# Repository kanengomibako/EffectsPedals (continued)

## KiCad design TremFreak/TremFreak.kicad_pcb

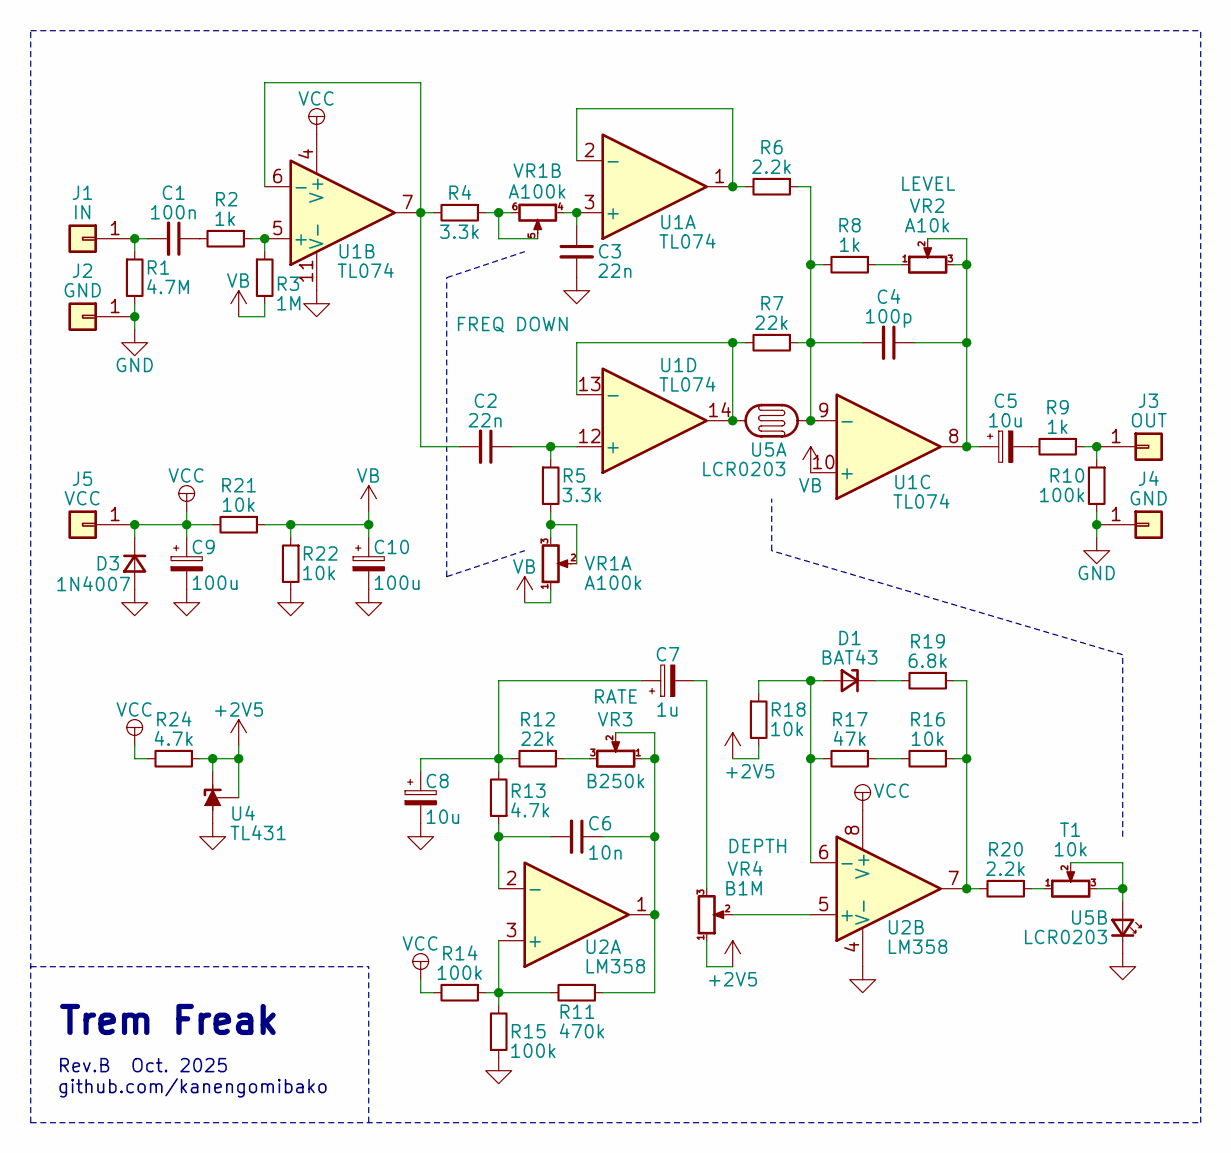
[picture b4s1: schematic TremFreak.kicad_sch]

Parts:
C1: 100n; my_C_Rect1_P5.00mm
C2, C3: 22n; my_C_Rect1_P5.00mm
C4: 100p; my_C_Rect1_P5.00mm
C5, C8: 10u; my_C_D5.0mm_P2.50mm
C6: 10n; my_C_Rect1_P5.00mm
C7: 1u; my_C_D5.0mm_P2.50mm
C9, C10: 100u; my_C_D6.3mm_P2.50mm
D1: BAT43; my_D_P7.62mm
D3: 1N4007; my_D_P7.62mm
J1: IN; my_WirePad_1mmDrill
J2, J4: GND; my_WirePad_1mmDrill
J3: OUT; my_WirePad_1mmDrill
J5: VCC; my_WirePad_1mmDrill
R1: 4.7M; my_R_P7.62mm_Horizontal
R2, R8, R9: 1k; my_R_P7.62mm_Horizontal
R3: 1M; my_R_P7.62mm_Horizontal
R4, R5: 3.3k; my_R_P7.62mm_Horizontal
R6, R20: 2.2k; my_R_P7.62mm_Horizontal
R7, R12: 22k; my_R_P7.62mm_Horizontal
R10, R14, R15: 100k; my_R_P7.62mm_Horizontal
R11: 470k; my_R_P7.62mm_Horizontal
R13, R24: 4.7k; my_R_P7.62mm_Horizontal
R16, R18, R21, R22: 10k; my_R_P7.62mm_Horizontal
R17: 47k; my_R_P7.62mm_Horizontal
R19: 6.8k; my_R_P7.62mm_Horizontal
T1: 10k; my_trim
U1: TL074; DIP-14_W7.62mm_Socket
U2: LM358; DIP-8_W7.62mm_Socket
U4: TL431; TO-92_Inline_Wide
U5: LCR0203
VR1: A100k; my_pot_5mm_dual
VR2: A10k; my_pot_5mm
VR3: B250k; my_pot_5mm
VR4: B1M; my_pot_5mm

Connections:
+2V5: R18.2, R24.1, U4.1 (REF), U4.3 (K), VR4.1
GND: C3.2, C8.2, C9.2, C10.2, D3.2 (A), J2.1, J4.1, R1.2, R10.2, R15.1, R22.2, U1.11 (V-), U2.4 (V-), U4.2 (A), U5.2
unnamed: C1.1, R2.2
unnamed: C4.1, C5.1, U1.8, VR2.2, VR2.3
unnamed: C5.2, R9.2
unnamed: C6.1, R11.1, U2.1, VR3.1, VR3.2
unnamed: C7.1, C8.1, R12.2, R13.2
unnamed: C7.2, VR4.3
unnamed: D1.2 (A), R17.2, R18.1, U2.6 (-)
unnamed: D1.1 (K), R19.2
unnamed: C1.2, J1.1, R1.1
unnamed: J3.1, R9.1, R10.1
unnamed: R4.1, VR1.5, VR1.6
unnamed: R5.2, VR1.2, VR1.3
unnamed: R8.1, VR2.1
unnamed: R12.1, VR3.3
unnamed: R16.1, R19.1, R20.2, U2.7
unnamed: R16.2, R17.1
unnamed: R20.1, T1.1
unnamed: T1.2, T1.3, U5.1
unnamed: C3.1, U1.3 (+), VR1.4
unnamed: R6.2, U1.1, U1.2 (-)
unnamed: R2.1, R3.1, U1.5 (+)
unnamed: C2.2, R4.2, U1.6 (-), U1.7
unnamed: C4.2, R6.1, R7.1, R8.2, U1.9 (-), U5.3
unnamed: C2.1, R5.1, U1.12 (+)
unnamed: R7.2, U1.13 (-), U1.14, U5.4
unnamed: R11.2, R14.1, R15.2, U2.3 (+)
unnamed: C6.2, R13.1, U2.2 (-)
unnamed: U2.5 (+), VR4.2
VB: C10.1, R3.2, R21.1, R22.1, U1.10 (+), VR1.1
VCC: C9.1, D3.1 (K), J5.1, R14.2, R21.2, R24.2, U1.4 (V+), U2.8 (V+)

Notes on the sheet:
Trem Freak
Rev.B Oct. 2025 github.com/kanengomibako

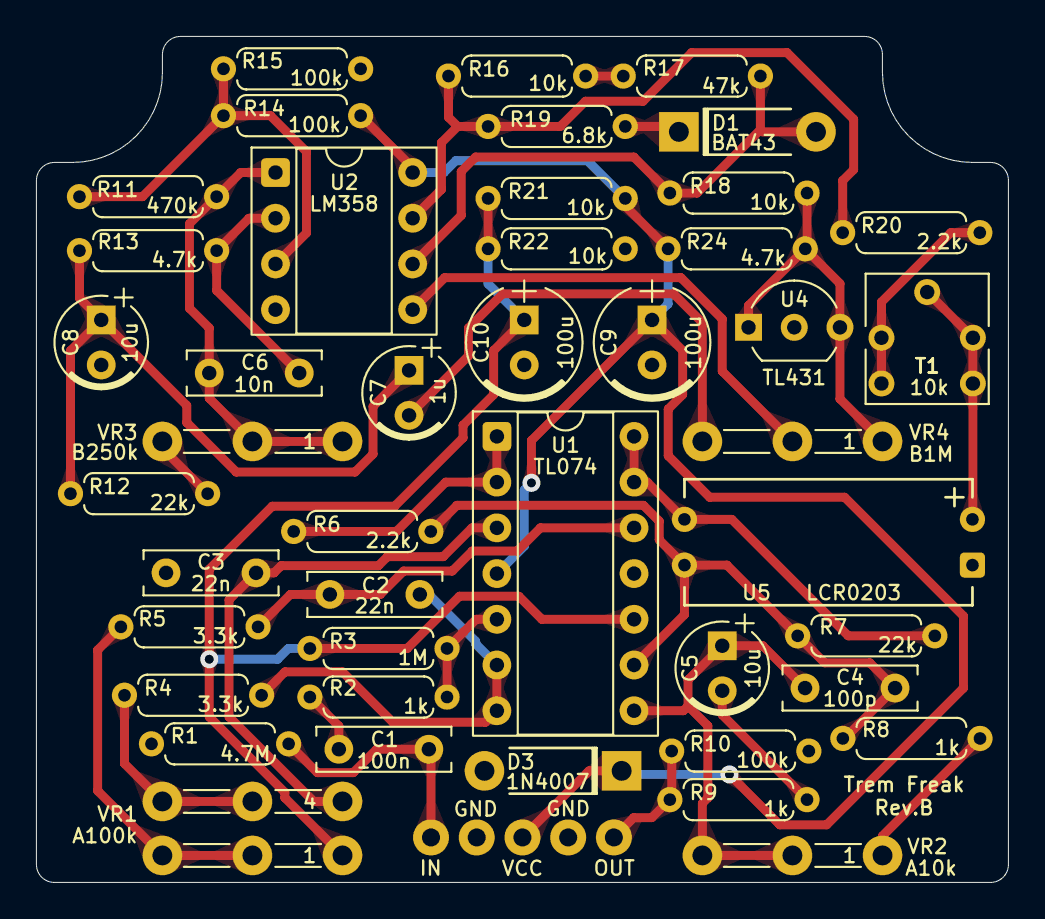
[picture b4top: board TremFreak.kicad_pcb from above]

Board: 2 copper layers, 54.0 x 47.0 mm, 49 parts (0 on the bottom side), 32 nets.

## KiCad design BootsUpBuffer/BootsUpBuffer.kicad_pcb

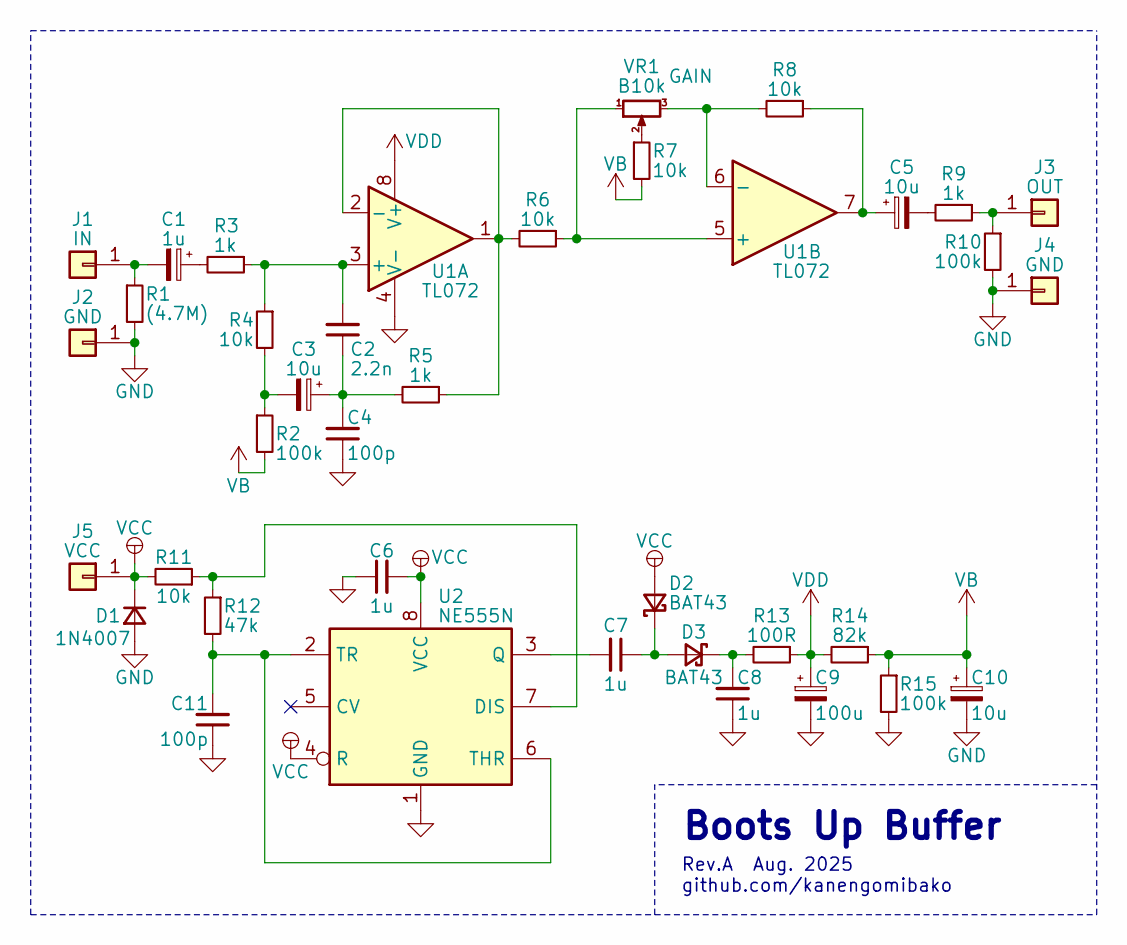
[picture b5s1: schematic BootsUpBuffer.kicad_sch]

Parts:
C1: 1u; my_C_D5.0mm_P2.50mm_long
C2: 2.2n; my_C_Rect1_P5.00mm
C3, C5, C10: 10u; my_C_D5.0mm_P2.50mm
C4, C11: 100p; my_C_Disc_P2.50mm
C6, C7, C8: 1u; my_C_Disc_P2.50mm
C9: 100u; my_C_D5.0mm_P2.50mm
D1: 1N4007; my_D_P7.62mm
D2, D3: BAT43; my_D_P7.62mm
J1: IN; my_WirePad_1mmDrill
J2, J4: GND; my_WirePad_1mmDrill
J3: OUT; my_WirePad_1mmDrill
J5: VCC; my_WirePad_1mmDrill
R1: (4.7M); my_R_P7mm_Horizontal
R2, R10, R15: 100k; my_R_P7mm_Horizontal
R3, R5, R9: 1k; my_R_P7mm_Horizontal
R4, R6, R7, R8, R11: 10k; my_R_P7mm_Horizontal
R12: 47k; my_R_P7mm_Horizontal
R13: 100R; my_R_P7mm_Horizontal
R14: 82k; my_R_P7mm_Horizontal
U1: TL072; DIP-8_W7.62mm_Socket
U2: NE555N; DIP-8_W7.62mm_Socket
VR1: B10k; my_pot_5mm

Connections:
GND: C4.1, C6.1, C8.1, C9.2, C10.2, C11.1, D1.2 (A), J2.1, J4.1, R1.2, R10.2, R15.2, U1.4 (V-), U2.1 (GND)
unnamed: C1.1, R3.2
unnamed: C2.1, C3.1, C4.2, R5.2
unnamed: C3.2, R2.1, R4.2
unnamed: C5.1, R8.1, U1.7
unnamed: C5.2, R9.2
unnamed: C7.1, D2.1 (K), D3.2 (A)
unnamed: C8.2, D3.1 (K), R13.2
unnamed: C1.2, J1.1, R1.1
unnamed: J3.1, R9.1, R10.1
unnamed 10: R7.1, VR1.2; also elsewhere on the board
unnamed: C2.2, R3.1, R4.1, U1.3 (+)
unnamed: R5.1, R6.2, U1.1, U1.2 (-)
unnamed 13: R6.1, U1.5 (+), VR1.1; also elsewhere on the board
unnamed 14: R8.2, U1.6 (-), VR1.3; also elsewhere on the board
unnamed: R11.1, R12.1, U2.7 (DIS)
unnamed: C7.2, U2.3 (Q)
unnamed: C11.2, R12.2, U2.2 (TR), U2.6 (THR)
VB: C10.1, R2.2, R7.2, R14.1, R15.1
VCC: C6.2, D1.1 (K), D2.2 (A), J5.1, R11.2, U2.4 (R), U2.8 (VCC)
VDD: C9.1, R13.1, R14.2, U1.8 (V+)

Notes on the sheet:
Boots Up Buffer
Rev.A Aug. 2025 github.com/kanengomibako

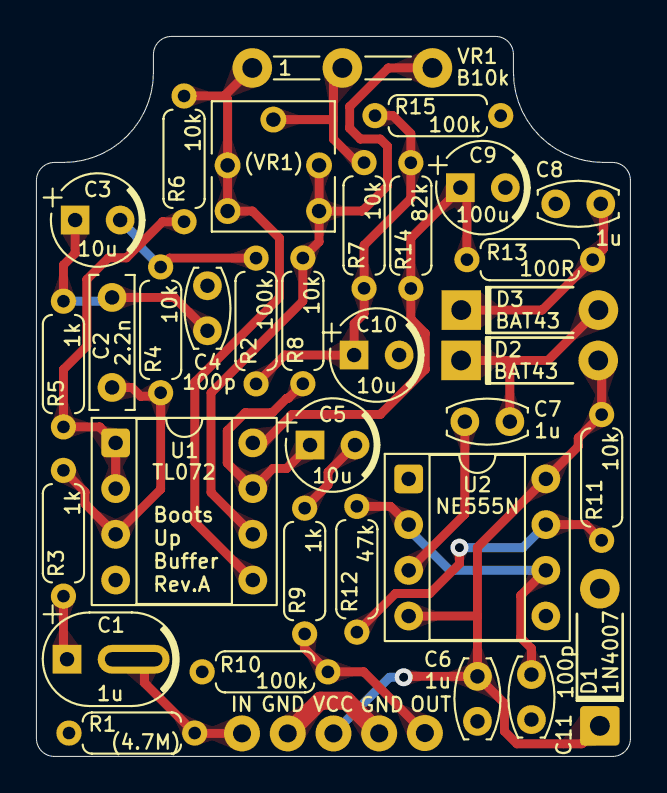
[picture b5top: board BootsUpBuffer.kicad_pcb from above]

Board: 2 copper layers, 33.0 x 40.0 mm, 38 parts (0 on the bottom side), 21 nets.

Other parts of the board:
*: (VR1); my_trim

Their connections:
unnamed 10: *.2; also elsewhere on the board
unnamed 13: *.1; also elsewhere on the board
unnamed 14: *.3; also elsewhere on the board

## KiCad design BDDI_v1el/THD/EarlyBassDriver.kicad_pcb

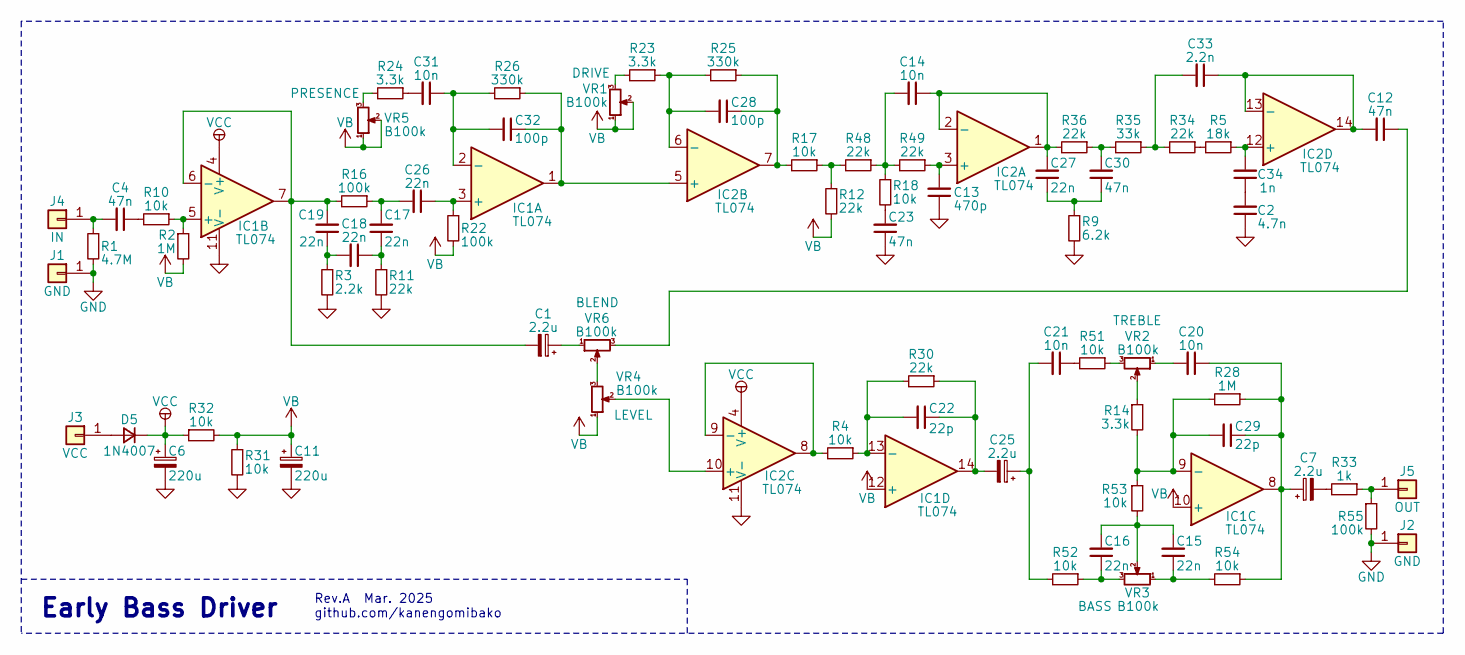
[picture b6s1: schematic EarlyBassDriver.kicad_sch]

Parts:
C1, C7, C25: 2.2u; my_C_D5.0mm_P2.50mm
C2: 4.7n; my_C_Rect1_P5.00mm
C4, C12, C23, C30: 47n; my_C_Rect1_P5.00mm
C6, C11: 220u; my_C_D6.3mm_P2.50mm
C13: 470p; my_C_Rect1_P5.00mm
C14, C20, C21, C31: 10n; my_C_Rect1_P5.00mm
C15, C16, C17, C18, C19, C26, C27: 22n; my_C_Rect1_P5.00mm
C22, C29: 22p; my_C_Rect1_P5.00mm
C28, C32: 100p; my_C_Rect1_P5.00mm
C33: 2.2n; my_C_Rect1_P5.00mm
C34: 1n; my_C_Rect1_P5.00mm
D5: 1N4007; my_D_P7.62mm
IC1, IC2: TL074; DIP-14_W7.62mm_Socket
J1, J2: GND; my_WirePad_0-8mmDrill
J3: VCC; my_WirePad_0-8mmDrill
J4: IN; my_WirePad_0-8mmDrill
J5: OUT; my_WirePad_0-8mmDrill
R1: 4.7M; my_R_P7.62mm_Horizontal
R2, R28: 1M; my_R_P7.62mm_Horizontal
R3: 2.2k; my_R_P7.62mm_Horizontal
R4, R10, R17, R18, R31, R32, R51, R52, R53, R54: 10k; my_R_P7.62mm_Horizontal
R5: 18k; my_R_P7.62mm_Horizontal
R9: 6.2k; my_R_P7.62mm_Horizontal
R11, R12, R30, R34, R36, R48, R49: 22k; my_R_P7.62mm_Horizontal
R14, R23, R24: 3.3k; my_R_P7.62mm_Horizontal
R16, R22, R55: 100k; my_R_P7.62mm_Horizontal
R25, R26: 330k; my_R_P7.62mm_Horizontal
R33: 1k; my_R_P7.62mm_Horizontal
R35: 33k; my_R_P7.62mm_Horizontal
VR1, VR2, VR3, VR4, VR5, VR6: B100k; my_pot_5mm

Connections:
GND: C2.1, C6.2, C11.2, C13.1, C23.1, IC1.11 (V-), IC2.11 (V-), J1.1, J2.1, R1.2, R3.2, R9.2, R11.2, R31.2, R55.2
unnamed: C1.1, VR6.1
unnamed: C2.2, C34.1
unnamed: C4.1, R10.2
unnamed: C7.2, R33.2
unnamed: C12.1, VR6.3
unnamed: C14.2, R18.1, R48.1, R49.2
unnamed: C15.1, R54.2, VR3.1
unnamed: C15.2, C16.2, R53.2, VR3.2
unnamed: C16.1, R52.1, VR3.3
unnamed: C17.1, C18.1, R11.1
unnamed: C17.2, C26.2, R16.1
unnamed: C18.2, C19.1, R3.1
unnamed: C7.1, C20.1, C29.1, IC1.8, R28.1, R54.1
unnamed: C20.2, VR2.1
unnamed: C21.1, R51.2
unnamed: C21.2, C25.1, R52.2
unnamed: C22.1, C25.2, IC1.14, R30.1
unnamed: C23.2, R18.2
unnamed: C27.1, C30.1, R9.1
unnamed: C28.1, IC2.7, R17.2, R25.1
unnamed: C30.2, R35.2, R36.1
unnamed: C31.2, R24.1
unnamed: C33.2, R34.2, R35.1
unnamed: D5.2 (A), J3.1
unnamed: C26.1, IC1.3 (+), R22.1
unnamed: C31.1, C32.2, IC1.2 (-), R26.2
unnamed: IC1.5 (+), R2.1, R10.1
unnamed: C1.2, C19.2, IC1.6 (-), IC1.7, R16.2
unnamed: C29.2, IC1.9 (-), R14.2, R28.2, R53.1
unnamed: C22.2, IC1.13 (-), R4.1, R30.2
unnamed: C13.2, IC2.3 (+), R49.1
unnamed: C14.1, C27.2, IC2.1, IC2.2 (-), R36.2
unnamed: C32.1, IC1.1, IC2.5 (+), R26.1
unnamed: C28.2, IC2.6 (-), R23.1, R25.2
unnamed: IC2.10 (+), VR4.2
unnamed: IC2.8, IC2.9 (-), R4.2
unnamed: C34.2, IC2.12 (+), R5.1
unnamed: C12.2, C33.1, IC2.13 (-), IC2.14
unnamed: C4.2, J4.1, R1.1
unnamed: J5.1, R33.1, R55.1
unnamed: R12.1, R17.1, R48.2
unnamed: R14.1, VR2.2
unnamed: R23.2, VR1.3
unnamed: R24.2, VR5.3
unnamed: R5.2, R34.1
unnamed: R51.1, VR2.3
unnamed: VR4.3, VR6.2
VB: C11.1, IC1.10 (+), IC1.12 (+), R2.2, R12.2, R22.2, R31.1, R32.2, VR1.1, VR1.2, VR4.1, VR5.1, VR5.2
VCC: C6.1, D5.1 (K), IC1.4 (V+), IC2.4 (V+), R32.1

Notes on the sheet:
Rev.A Mar. 2025 github.com/kanengomibako
Early Bass Driver

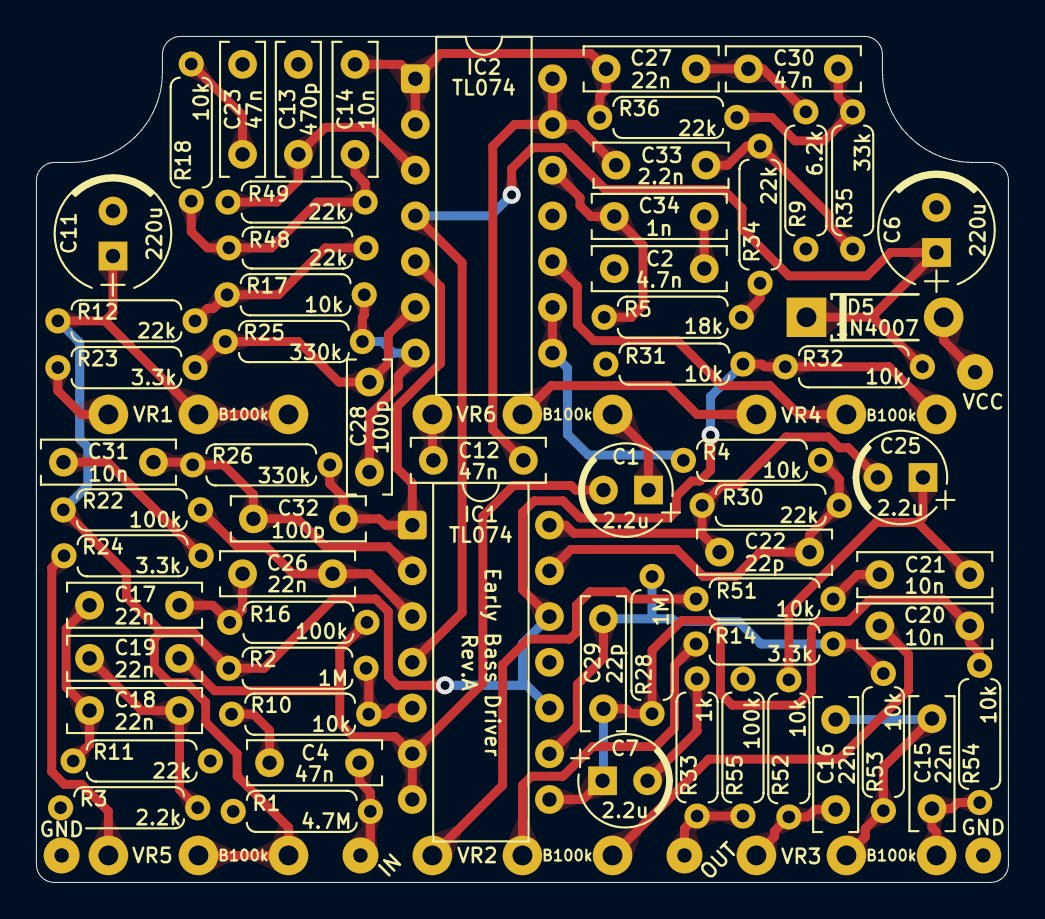
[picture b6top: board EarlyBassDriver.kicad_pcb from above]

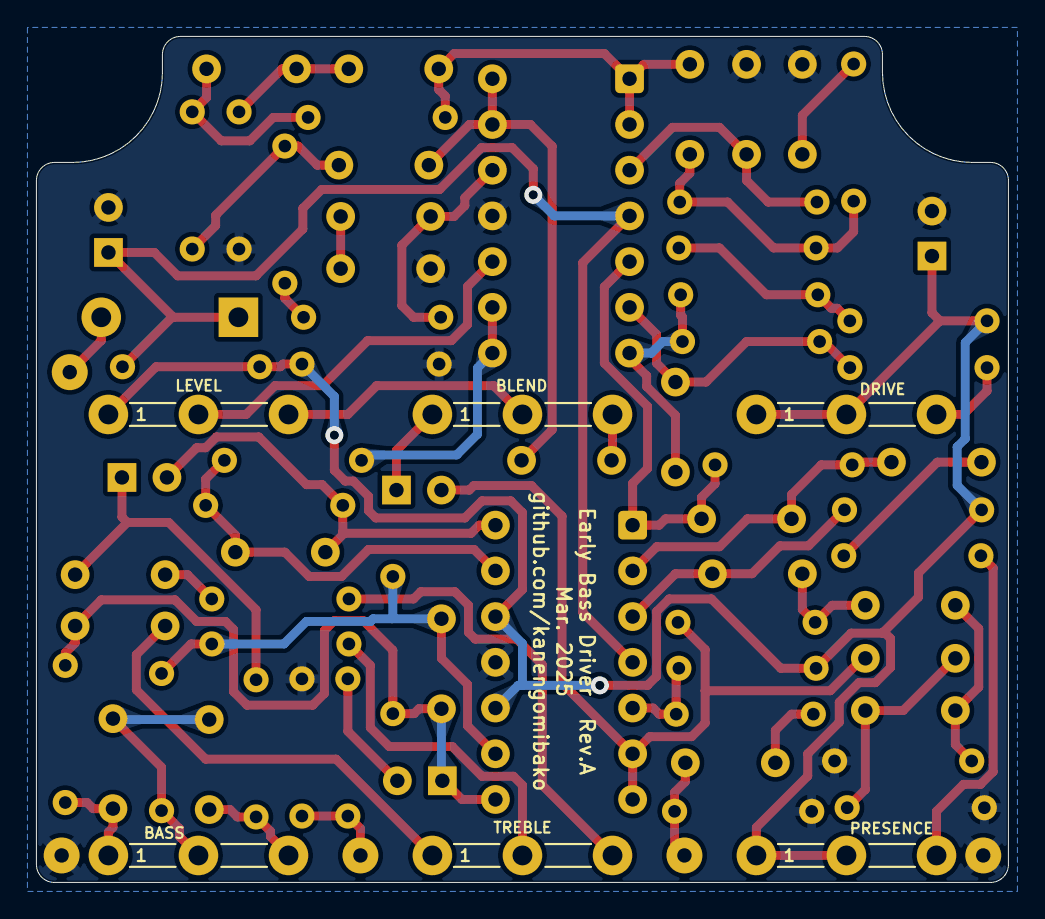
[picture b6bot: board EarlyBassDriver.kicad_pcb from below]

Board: 2 copper layers, 54.0 x 47.0 mm, 75 parts (6 on the bottom side), 50 nets.

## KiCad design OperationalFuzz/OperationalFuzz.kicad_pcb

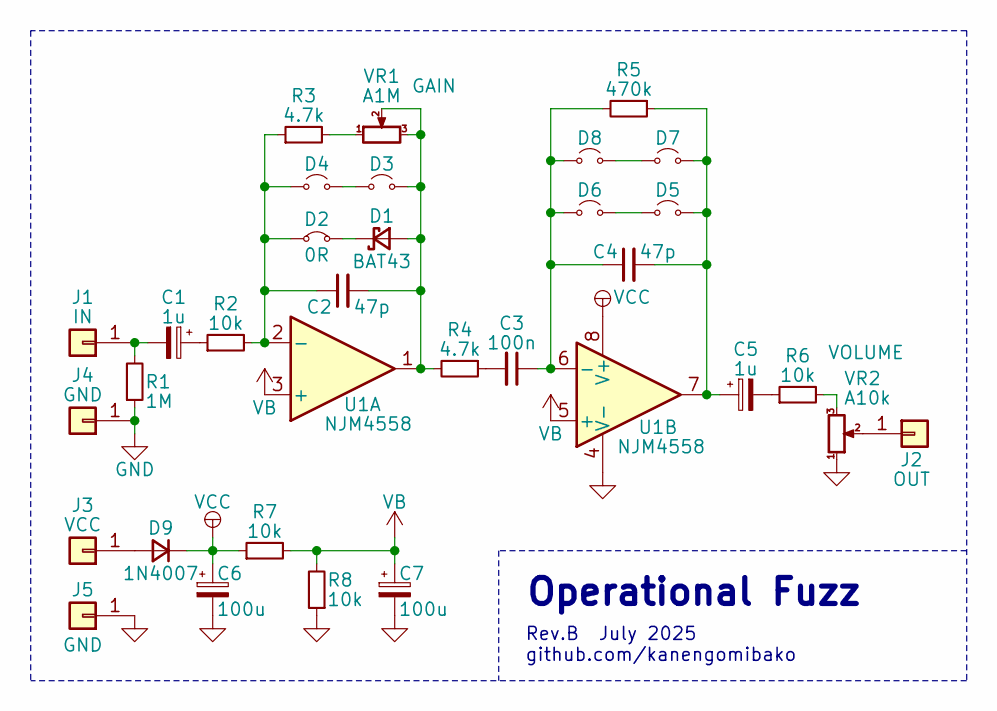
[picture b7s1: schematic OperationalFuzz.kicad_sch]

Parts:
C1, C5: 1u; my_C_D5.0mm_P2.50mm
C2, C4: 47p; my_C_Rect1_P5.00mm
C3: 100n; my_C_Rect1_P5.00mm
C6, C7: 100u; my_C_D6.3mm_P2.50mm
D1: BAT43; my_D_P7.62mm
D2: 0R; my_D_P7.62mm
D3, D4, D5, D6, D7, D8: x; my_D_P7.62mm
D9: 1N4007; my_D_P7.62mm
J1: IN; PinHeader_1x01_P2.54mm_Vertical
J2: OUT; PinHeader_1x01_P2.54mm_Vertical
J3: VCC; PinHeader_1x01_P2.54mm_Vertical
J4, J5: GND; PinHeader_1x01_P2.54mm_Vertical
R1: 1M; my_R_P7.62mm_Horizontal
R2, R6, R7, R8: 10k; my_R_P7.62mm_Horizontal
R3, R4: 4.7k; my_R_P7.62mm_Horizontal
R5: 470k; my_R_P7.62mm_Horizontal
U1: NJM4558; DIP-8_W7.62mm_Socket
VR1: A1M; my_pot_5mm
VR2: A10k; my_pot_5mm

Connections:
GND: C6.2, C7.2, J4.1, J5.1, R1.1, R8.1, U1.4 (V-), VR2.1
unnamed: C1.1, R2.1
unnamed: C3.2, R4.1
unnamed: C5.2, R6.1
unnamed: C2.2, D1.2 (A), D3.1 (A), R4.2, U1.1, VR1.2, VR1.3
unnamed: D1.1 (K), D2.2 (B)
unnamed: C2.1, D2.1 (A), D4.2 (B), R2.2, R3.1, U1.2 (-)
unnamed: D3.2 (B), D4.1 (A)
unnamed: D5.1 (A), D6.2 (B)
unnamed: C4.2, C5.1, D5.2 (B), D7.1 (A), R5.1, U1.7
unnamed: C3.1, C4.1, D6.1 (A), D8.2 (B), R5.2, U1.6 (-)
unnamed: D7.2 (B), D8.1 (A)
unnamed: D9.2 (A), J3.1
unnamed: C1.2, J1.1, R1.2
unnamed: J2.1, VR2.2
unnamed: R3.2, VR1.1
unnamed: R6.2, VR2.3
VB: C7.1, R7.2, R8.2, U1.3 (+), U1.5 (+)
VCC: C6.1, D9.1 (K), R7.1, U1.8 (V+)

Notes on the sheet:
Operational Fuzz
Rev.B July 2025 github.com/kanengomibako

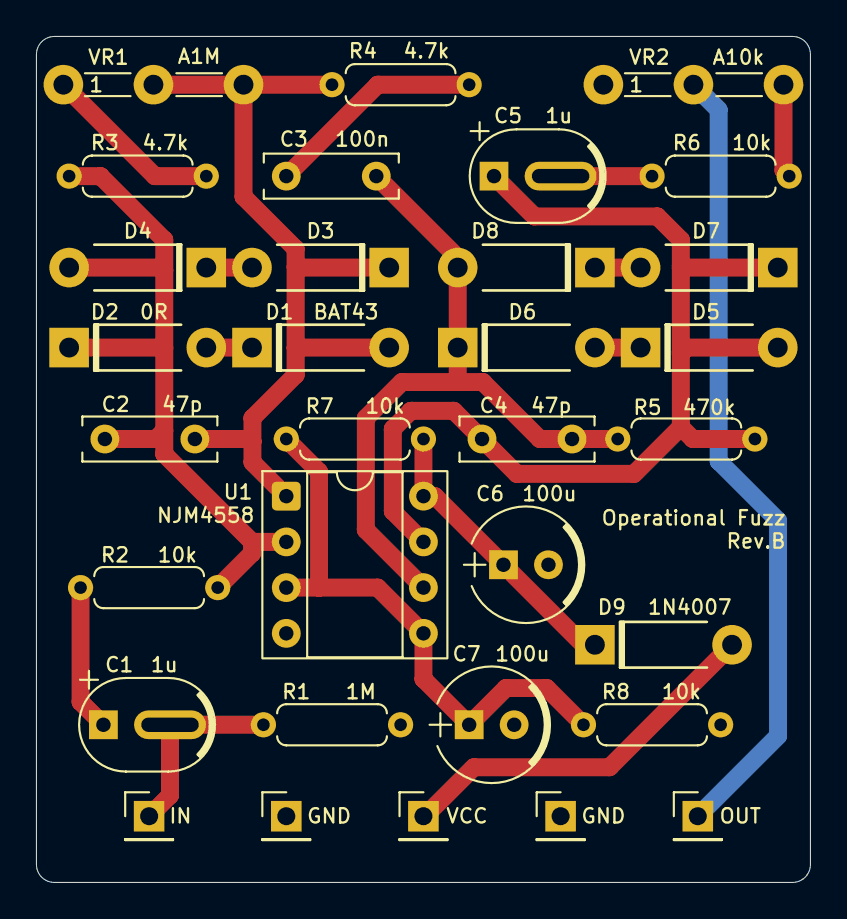
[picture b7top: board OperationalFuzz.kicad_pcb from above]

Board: 2 copper layers, 43.0 x 47.0 mm, 32 parts (0 on the bottom side), 19 nets.

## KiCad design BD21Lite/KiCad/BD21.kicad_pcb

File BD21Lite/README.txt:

BD21 Lite (True Bypass)

製作記事→https://kanengomibako.github.io/pages/00049.html

BEHRINGER BDI21を簡略化したエフェクターです。XLR OUTPUTやPARALLEL OUTPUTはなく、トゥルーバイパス用です。

ポットの配線をしなくていいようなレイアウトにしました。ポットの間隔は、横18mm、縦25mmです。HAMMOND1590Bサイズで電池を入れることもできます。

かなりパーツ同士の感覚が狭いので、大きめの部品を使うのは無理そうです。左下のあたりは特に狭くなっており、R1(1M)は5mm程度浮かして取り付けることをお勧めします。文字が潰れて見にくいところはBD21Lite_parts.pngで確認できます。

＜パーツリスト＞
33p	2	C22, C23
220p	2	C12, C13
470p	1	C9
1n	1	C10
2.2n	1	C2
10n	4	C1, C11, C18, C19
22n	8	C3, C4, C5, C6, C7, C16, C27, C29
47n	3	C8, C14, C15
100n	1	C25
100n*	2	C98, C99 *Multi-Layer Ceramic Capacitor
2.2u	1	C20
220u	2	C31, C32

1k	1	R28
2.2k	1	R14
3.3k	3	R16, R17, R31
6.2k	1	R21
10k	9	R2, R6, R7, R33, R37, R40, R42, R45, R46
22k	6	R5, R8, R11, R15, R18, R29
33k	1	R9
39k	1	R10
100k	3	R3, R4, R27
330k	2	R12, R13
1M	2	R1, R32
2.2M	1	R99

100kB	6	RV19, RV20, RV22, RV24, RV26, RV41

1N4007	1	D1
TL074	2	U1, U2

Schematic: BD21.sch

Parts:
C1, C11, C18, C19: 10n; my_C_Rect1_P5.00mm
C2: 2.2n; my_C_Rect1_P5.00mm
C3, C4, C5, C6, C7, C16, C27, C29: 22n; my_C_Rect1_P5.00mm
C8, C14, C15: 47n; my_C_Rect1_P5.00mm
C9: 470p; my_C_Rect1_P5.00mm
C10: 1n; my_C_Rect1_P5.00mm
C12, C13: 220p; my_C_Rect1_P5.00mm
C20: 2.2u; my_C_D5.0mm_P2.50mm
C22, C23: 33p; my_C_Disc_P2.50mm
C25: 100n; my_C_Rect1_P5.00mm
C31, C32: 220u; my_C_D8mm_P3.5mm
C98, C99: 100n; my_C_Disc_P2.50mm
D1: 1N4007; D_DO-41_SOD81_P7.62mm_Horizontal
J1: IN; my_WirePad_0-8mmDrill
J4: OUT; my_WirePad_0-8mmDrill
J7: 9V; my_WirePad_0-8mmDrill
J10: GND; my_WirePad_0-8mmDrill
R1, R32: 1M; my_R_P7.62mm_Horizontal
R2, R6, R7, R33, R37, R40, R42, R45, R46: 10k; my_R_P7.62mm_Horizontal
R3, R4, R27: 100k; my_R_P7.62mm_Horizontal
R5, R8, R11, R15, R18, R29: 22k; my_R_P7.62mm_Horizontal
R9: 33k; my_R_P7.62mm_Horizontal
R10: 39k; my_R_P7.62mm_Horizontal
R12, R13: 330k; my_R_P7.62mm_Horizontal
R14: 2.2k; my_R_P7.62mm_Horizontal
R16, R17, R31: 3.3k; my_R_P7.62mm_Horizontal
R21: 6.2k; my_R_P7.62mm_Horizontal
R28: 1k; my_R_P7.62mm_Horizontal
R99: 2.2M; my_R_P7.62mm_Horizontal
RV19, RV20, RV22, RV24, RV26, RV41: 100kB; my_pot_5mm
U1, U2: TL074; DIP-14_W7.62mm

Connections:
/VB: C8.2, C9.2, C10.2, C32.1, R1.1, R4.1, R11.1, R14.1, R15.1, R21.1, R45.1, R46.2, RV19.1, RV19.2, RV20.1, RV20.2, RV26.1, U1.3 (+), U1.5 (+)
GND: C31.2, C32.2, C98.2, C99.2, D1.2, J10.1, R27.1, R46.1, R99.2, U1.11 (V-), U2.11 (V-); also elsewhere on the board
unnamed: C1.1, C16.1, R18.2, U2.8, U2.9 (-)
unnamed: C1.2, R5.1, R7.2, R8.2
unnamed: C2.2, R9.1, R10.2
unnamed: C3.1, R2.2
unnamed: C3.2, J1.1, R99.1
unnamed: C4.1, R4.2, U1.10 (+)
unnamed: C4.2, C7.1, R3.1
unnamed: C5.1, R3.2, RV22.1, U1.13 (-), U1.14
unnamed: C5.2, C6.2, R14.2
unnamed: C6.1, C7.2, R15.2
unnamed: C8.1, R7.1
unnamed: C9.1, R8.1, U2.10 (+)
unnamed: C10.1, R10.1, U2.5 (+)
unnamed: C11.1, C12.2, R12.2, U1.9 (-)
unnamed: C11.2, R17.2
unnamed: C12.1, R12.1, U1.8, U2.12 (+)
unnamed: C13.1, R6.2, R13.1, U2.14
unnamed: C13.2, R13.2, R16.2, U2.13 (-)
unnamed: C2.1, C14.1, U2.6 (-), U2.7
unnamed: C14.2, RV22.3
unnamed: C15.1, R9.2, R18.1
unnamed: C15.2, C16.2, R21.2
unnamed: C18.1, RV24.3
unnamed: C18.2, C25.1, R40.2
unnamed: C19.1, C20.1, C23.1, R32.1, R42.1, U1.1
unnamed: C19.2, RV24.1
unnamed: C20.2, R27.2, R28.2
unnamed: C22.1, C25.2, R29.1, U1.7
unnamed: C22.2, R29.2, R33.1, U1.6 (-)
unnamed: C23.2, R31.1, R32.2, R37.2, U1.2 (-)
unnamed: C27.1, C29.1, R37.1, RV41.2
unnamed: C27.2, R42.2, RV41.1
unnamed: C29.2, R40.1, RV41.3
unnamed: J4.1, R28.1
unnamed: R1.2, R2.1, U1.12 (+)
unnamed: R5.2, R6.1, R11.2
unnamed: R16.1, RV20.3
unnamed: R17.1, RV19.3
unnamed: R31.2, RV24.2
unnamed: R33.2, U2.1, U2.2 (-)
unnamed: RV22.2, RV26.3
unnamed: RV26.2, U2.3 (+)
VCC: C31.1, C98.1, C99.1, D1.1, J7.1, R45.2, U1.4 (V+), U2.4 (V+); also elsewhere on the board

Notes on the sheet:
BD21 Lite (True Bypass) June 2019 drugscore.blog.fc2.com
C17 and R27b are deleted D1, C98, C99 and R99 are added
Drive
Presence
Blend
Level
Bass
Treble

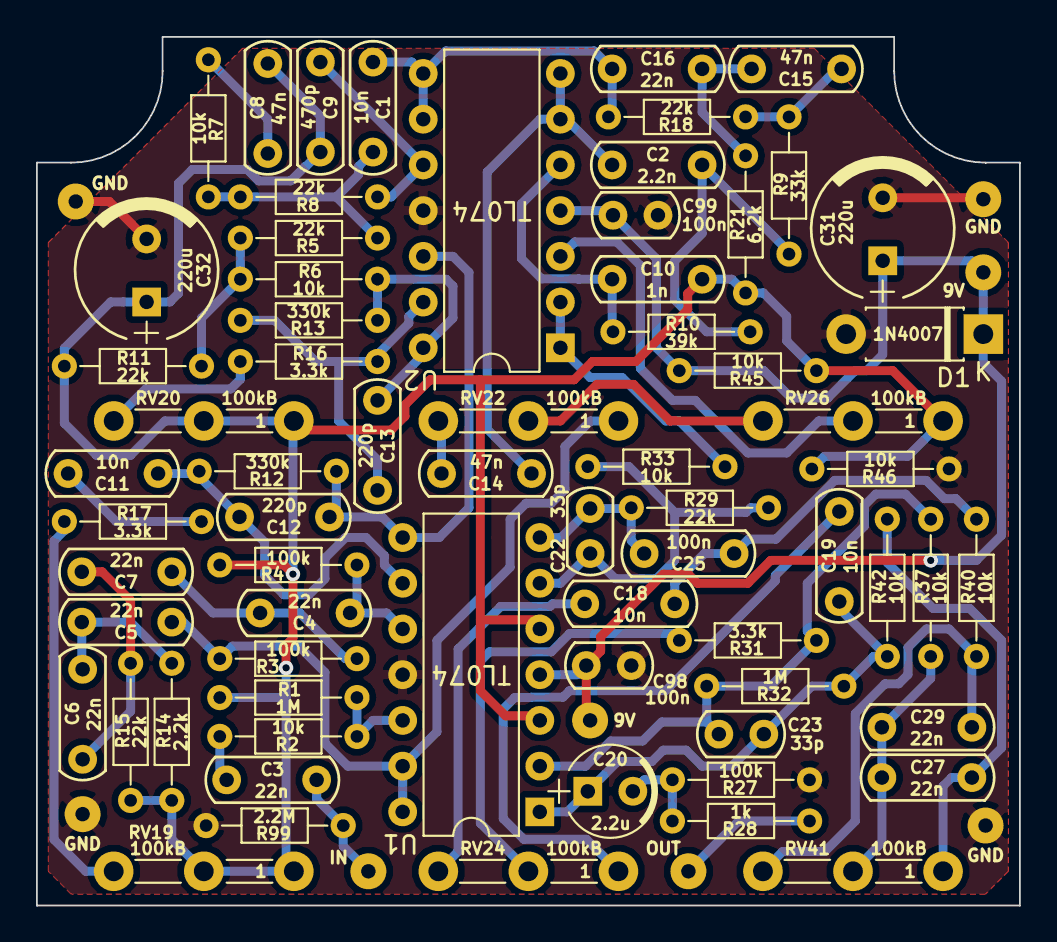
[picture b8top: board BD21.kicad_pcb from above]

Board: 2 copper layers, 54.6 x 48.3 mm, 76 parts (0 on the bottom side), 45 nets.

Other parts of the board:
J7#2: 9V; my_WirePad_0-8mmDrill
J10#2, J10#3, J10#4: GND; my_WirePad_0-8mmDrill

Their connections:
GND: J10#2.1, J10#3.1, J10#4.1; also elsewhere on the board
VCC: J7#2.1; also elsewhere on the board

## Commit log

2025-07-04 Add E6 Delay
2025-07-05 Move folders
2025-08-07 Add Operational Fuzz
2025-08-07 Move SMD version, add THD version
2025-08-22 Add Boots Up Buffer
2025-09-27 Update Template
2025-10-18 Add Trem Freak
2026-01-01 Add DT-1TB
2026-04-21 Add Pedal Meeting Headphone Amp
2026-05-25 Add Buffer Variator
2026-05-30 Add Buffer Variator data
